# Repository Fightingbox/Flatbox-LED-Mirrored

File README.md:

# Flatbox-LED-Mirrored
Based on the [GP2040-CE](https://github.com/OpenStickCommunity/GP2040-CE) Flatbox Rev4

Add the colorful LEDs and the OLED display, perfect hardware change beased on the [Flatbox](https://github.com/jfedor2/flatbox) design by [jfedor2](https://github.com/jfedor2) powered by an RP2040 MCU.

## Upgrade the firmware:
- Unplug your device.
- Put your device into Bootsel/USB mode. A new removable drive named RPI-RP2 should appear in your file explorer.
- Drag and drop the GP2040-CE_XXX.uf2 firmware into the removable drive.
- Wait for the device to automatically disconnect.

### If you encounter problems updating firmware, please refer to the official firmware update [Tutorial](https://gp2040-ce.info/?spm=a2g0o.detail.1000023.2.163cu936u936KZ#/installation).

## GP2040-CE Links

[Downloads](https://gp2040-ce.info/#/download) | [Installation](https://gp2040-ce.info/#/installation) | [Wiring](https://gp2040-ce.info/#/wiring) | [Usage](https://gp2040-ce.info/#/usage) | [FAQ](https://gp2040-ce.info/#/faq) | [GitHub](https://github.com/OpenStickCommunity/GP2040-CE)

Full documentation can be found at <https://gp2040-ce.info>

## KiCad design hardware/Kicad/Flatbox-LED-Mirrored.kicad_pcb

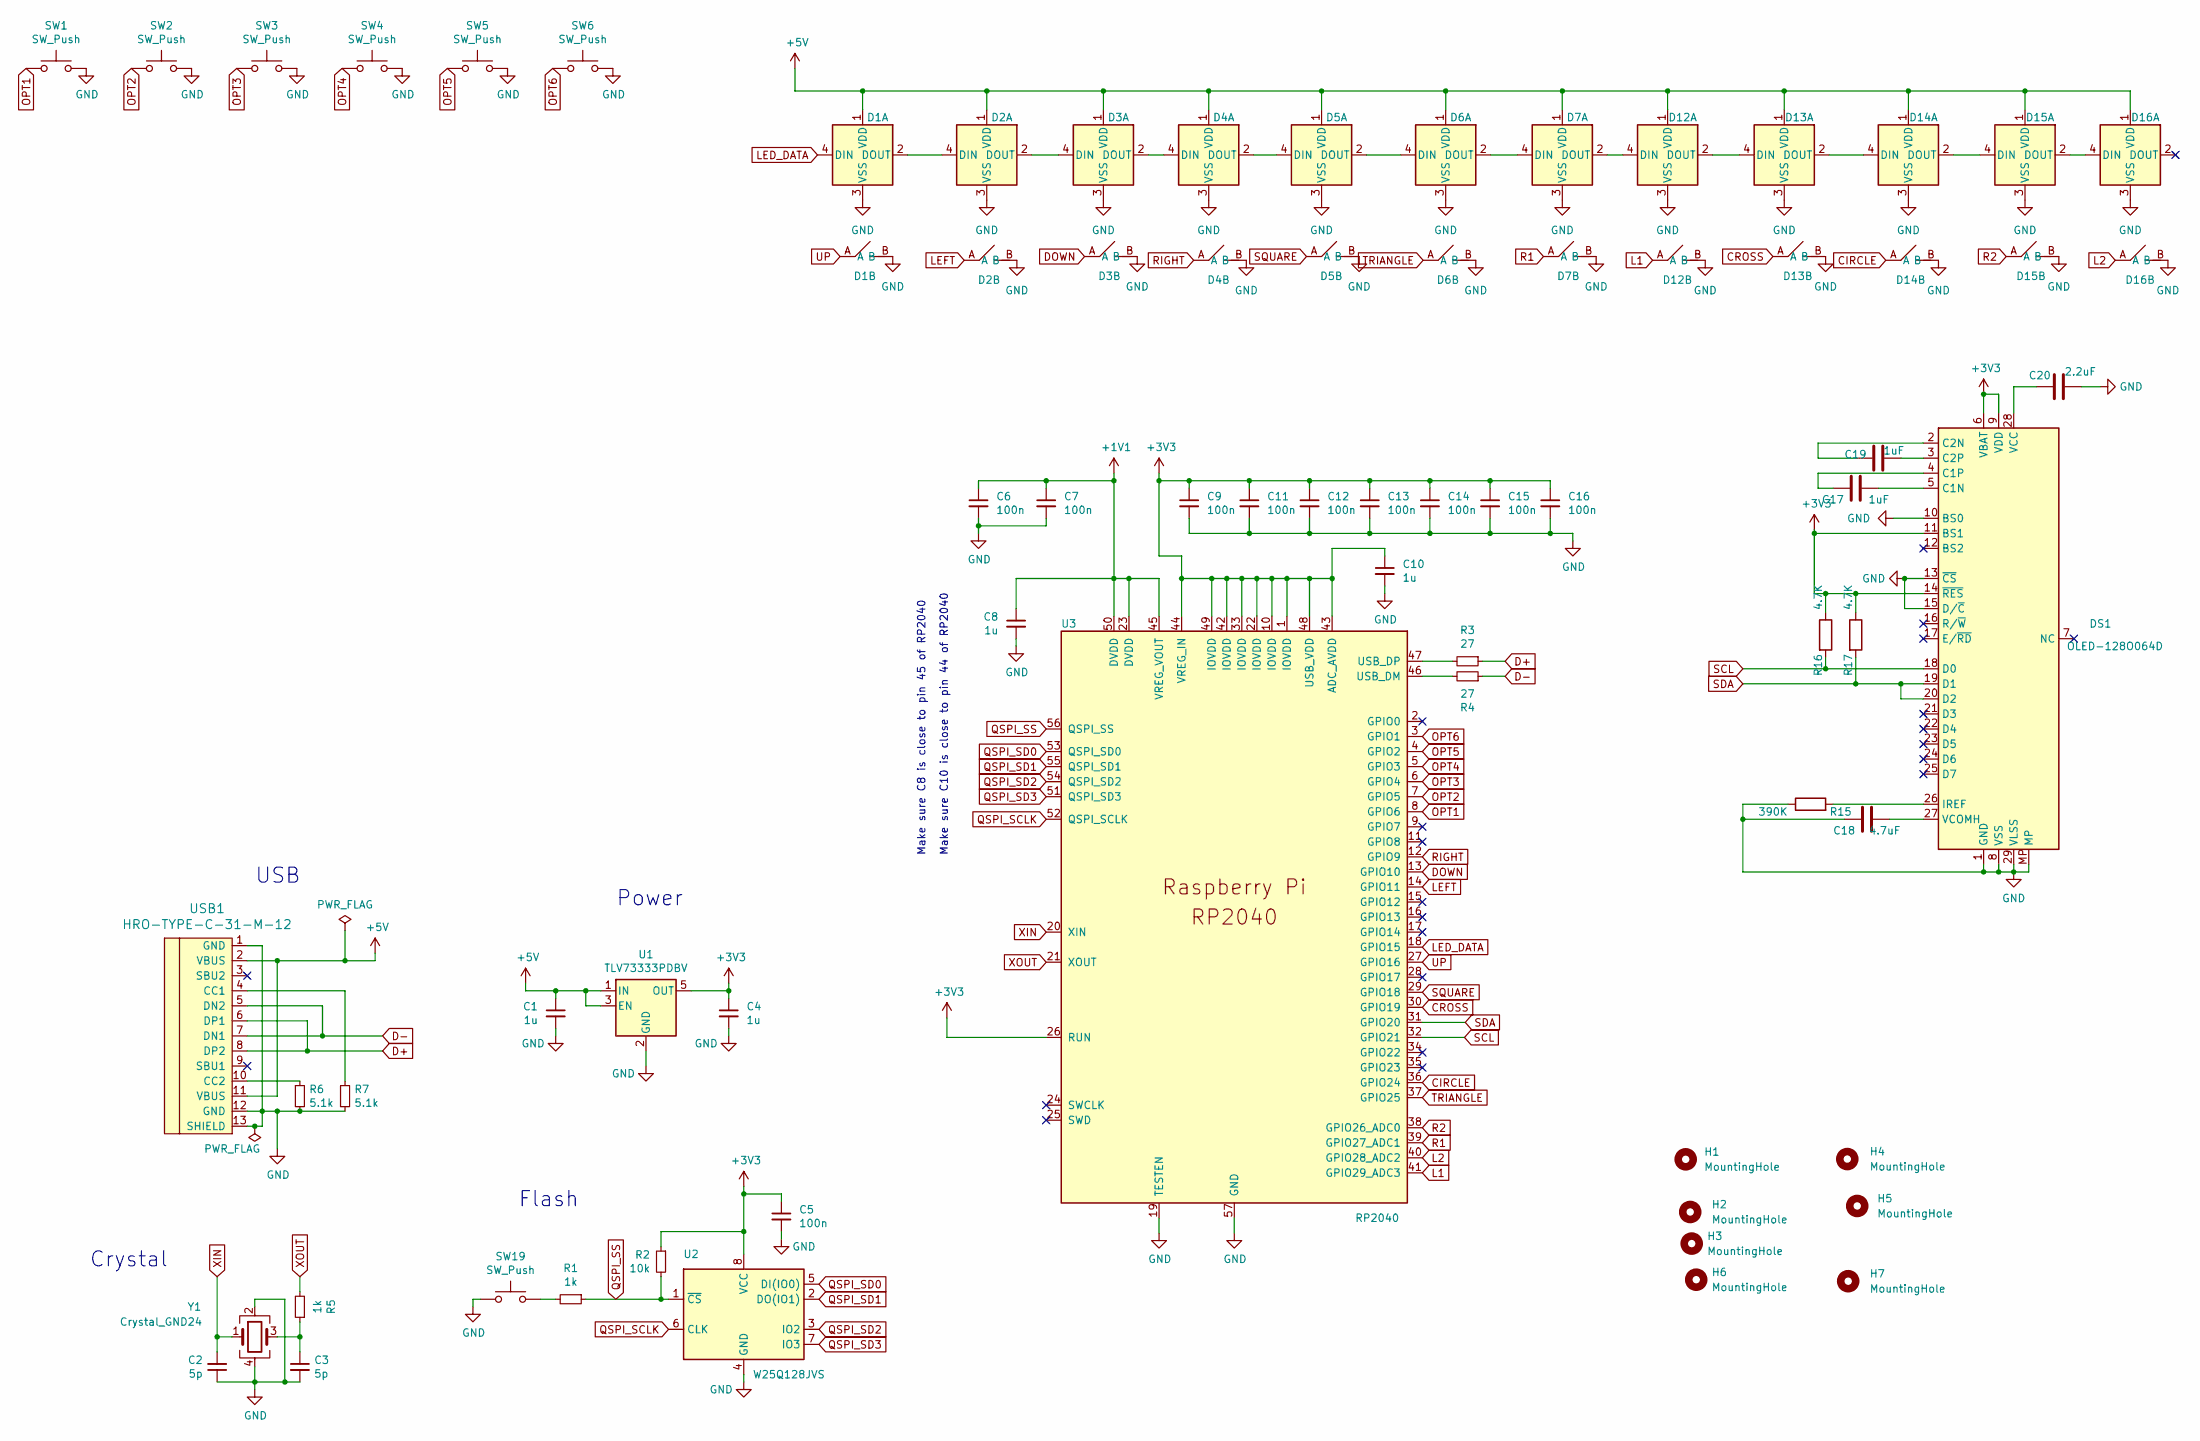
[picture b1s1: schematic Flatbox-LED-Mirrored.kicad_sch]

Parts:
C1, C4, C8, C10: 1u; C_0402_1005Metric; LCSC C52923
C2, C3: 5p; C_0402_1005Metric; LCSC C1570
C5, C6, C7, C9, C11, C12, C13, C14, C15, C16: 100n; C_0402_1005Metric; LCSC C1525
C17, C19: 1uF; C_0402_1005Metric
C18: 4.7uF; C_0603_1608Metric
C20: 2.2uF; C_0603_1608Metric
D1, D2, D3, D4, D5, D6, D7, D12, D13, D14, D15, D16: KB_HOTSWAP_WS2812B; Kailh_socket_PG1353_LED_1U
DS1: OLED-128O064D; TE_CON-0_1x30-1MP_P0.5mm_Horizontal-OLED-FPC
H1, H2, H3, H4, H5, H6, H7: MountingHole; MountingHole_6mm
R1, R5: 1k; R_0402_1005Metric; LCSC C11702
R2: 10k; R_0402_1005Metric; LCSC C25744
R3, R4: 27; R_0402_1005Metric; LCSC C138021
R6, R7: 5.1k; R_0402_1005Metric; LCSC C25905
R15: 390K; R_0402_1005Metric
R16, R17: 4.7K; R_0402_1005Metric
SW1, SW2, SW3, SW4, SW5, SW6: SW_Push; SW_Push_1P1T_NO_6x6mm_H5mm
SW19: SW_Push; SW-K2-1109SE; LCSC C271750
U1: TLV73333PDBV; SOT-23-5; LCSC C134139
U2: W25Q128JVS; SOIC-8_5.23x5.23mm_P1.27mm; LCSC C97521
U3: RP2040; RP2040-QFN-56; LCSC C2040
USB1: HRO-TYPE-C-31-M-12; HRO-TYPE-C-31-M-12-Assembly; LCSC C165948
Y1: Crystal_GND24; Crystal_SMD_3225-4Pin_3.2x2.5mm; LCSC C9002

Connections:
+1V1: C6.1, C7.1, C8.1, U3.23 (DVDD), U3.45 (VREG_VOUT), U3.50 (DVDD)
+3V3: C4.1, C5.1, C9.1, C10.1, C11.1, C12.1, C13.1, C14.1, C15.1, C16.1, DS1.6 (VBAT), DS1.9 (VDD), DS1.11 (BS1), DS1.14 (~RES), R2.1, R16.1, R17.1, U1.5 (OUT), U2.8 (VCC), U3.1 (IOVDD), U3.10 (IOVDD), U3.22 (IOVDD), U3.26 (RUN), U3.33 (IOVDD), U3.42 (IOVDD), U3.43 (ADC_AVDD), U3.44 (VREG_IN), U3.48 (USB_VDD), U3.49 (IOVDD)
+5V: C1.1, D1.1 (VDD), D2.1 (VDD), D3.1 (VDD), D4.1 (VDD), D5.1 (VDD), D6.1 (VDD), D7.1 (VDD), D12.1 (VDD), D13.1 (VDD), D14.1 (VDD), D15.1 (VDD), D16.1 (VDD), U1.1 (IN), U1.3 (EN), USB1.2 (VBUS), USB1.11 (VBUS)
CIRCLE: D14.A, U3.36 (GPIO24)
CROSS: D13.A, U3.30 (GPIO19)
D+: R3.1, USB1.6 (DP1), USB1.8 (DP2)
D-: R4.1, USB1.5 (DN2), USB1.7 (DN1)
DOWN: D3.A, U3.13 (GPIO10)
GND: C1.2, C2.1, C3.2, C4.2, C5.2, C6.2, C7.2, C8.2, C9.2, C10.2, C11.2, C12.2, C13.2, C14.2, C15.2, C16.2, C18.1, C20.2, D1.3 (VSS), D1.B, D2.3 (VSS), D2.B, D3.3 (VSS), D3.B, D4.3 (VSS), D4.B, D5.3 (VSS), D5.B, D6.3 (VSS), D6.B, D7.3 (VSS), D7.B, D12.3 (VSS), D12.B, D13.3 (VSS), D13.B, D14.3 (VSS), D14.B, D15.3 (VSS), D15.B, D16.3 (VSS), D16.B, DS1.1 (GND), DS1.8 (VSS), DS1.10 (BS0), DS1.13 (~CS), DS1.15 (D/~C), DS1.29 (VLSS), DS1.30 (GND), DS1.MP, R6.2, R7.2, R15.1, SW1.2, SW2.2, SW3.2, SW4.2, SW5.2, SW6.2, SW19.1, SW19.GND, U1.2 (GND), U2.4 (GND), U3.19 (TESTEN), U3.57 (GND), USB1.1 (GND), USB1.12 (GND), USB1.13 (SHIELD), Y1.2, Y1.4
L1: D12.A, U3.41 (GPIO29_ADC3)
L2: D16.A, U3.40 (GPIO28_ADC2)
LED_DATA: D1.4 (DIN), U3.18 (GPIO15)
unnamed: C3.1, R5.1, Y1.3
unnamed: D1.2 (DOUT), D2.4 (DIN)
unnamed: D2.2 (DOUT), D3.4 (DIN)
unnamed: D3.2 (DOUT), D4.4 (DIN)
unnamed: D4.2 (DOUT), D5.4 (DIN)
unnamed: D5.2 (DOUT), D6.4 (DIN)
unnamed: D6.2 (DOUT), D7.4 (DIN)
unnamed: D7.2 (DOUT), D12.4 (DIN)
unnamed: D12.2 (DOUT), D13.4 (DIN)
unnamed: D13.2 (DOUT), D14.4 (DIN)
unnamed: D14.2 (DOUT), D15.4 (DIN)
unnamed: D15.2 (DOUT), D16.4 (DIN)
unnamed: C17.2, DS1.5 (C1N)
unnamed: C17.1, DS1.4 (C1P)
unnamed: C19.1, DS1.2 (C2N)
unnamed: C19.2, DS1.3 (C2P)
unnamed: DS1.26 (IREF), R15.2
unnamed: C20.1, DS1.28 (VCC)
unnamed: C18.2, DS1.27 (VCOMH)
unnamed: R1.2, SW19.2
unnamed: R4.2, U3.46 (USB_DM)
unnamed: R3.2, U3.47 (USB_DP)
unnamed: R7.1, USB1.4 (CC1)
unnamed: R6.1, USB1.10 (CC2)
OPT1: SW1.1, U3.8 (GPIO6)
OPT2: SW2.1, U3.7 (GPIO5)
OPT3: SW3.1, U3.6 (GPIO4)
OPT4: SW4.1, U3.5 (GPIO3)
OPT5: SW5.1, U3.4 (GPIO2)
OPT6: SW6.1, U3.3 (GPIO1)
QSPI_SCLK: U2.6 (CLK), U3.52 (QSPI_SCLK)
QSPI_SD0: U2.5 (DI(IO0)), U3.53 (QSPI_SD0)
QSPI_SD1: U2.2 (DO(IO1)), U3.55 (QSPI_SD1)
QSPI_SD2: U2.3 (IO2), U3.54 (QSPI_SD2)
QSPI_SD3: U2.7 (IO3), U3.51 (QSPI_SD3)
QSPI_SS: R1.1, R2.2, U2.1 (~CS), U3.56 (QSPI_SS)
R1: D7.A, U3.39 (GPIO27_ADC1)
R2: D15.A, U3.38 (GPIO26_ADC0)
SCL: DS1.18 (D0), R16.2, U3.32 (GPIO21)
SDA: DS1.19 (D1), DS1.20 (D2), R17.2, U3.31 (GPIO20)
SQUARE: D5.A, U3.29 (GPIO18)
TRIANGLE: D6.A, U3.37 (GPIO25)
UP: D1.A, U3.27 (GPIO16)
XIN: C2.2, U3.20 (XIN), Y1.1
XOUT: R5.2, U3.21 (XOUT)

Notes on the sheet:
Make sure C10 is close to pin 44 of RP2040
Crystal
Flash
Make sure C8 is close to pin 45 of RP2040
USB
Power

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
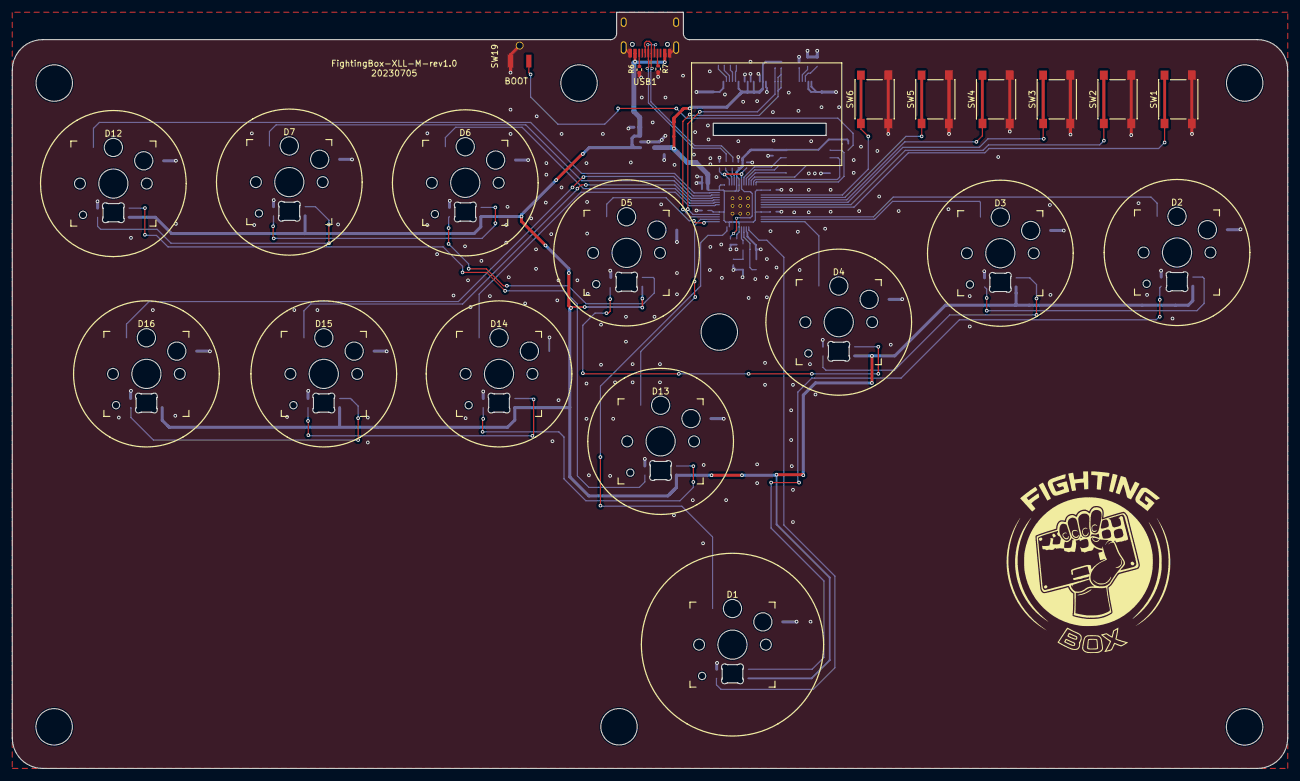
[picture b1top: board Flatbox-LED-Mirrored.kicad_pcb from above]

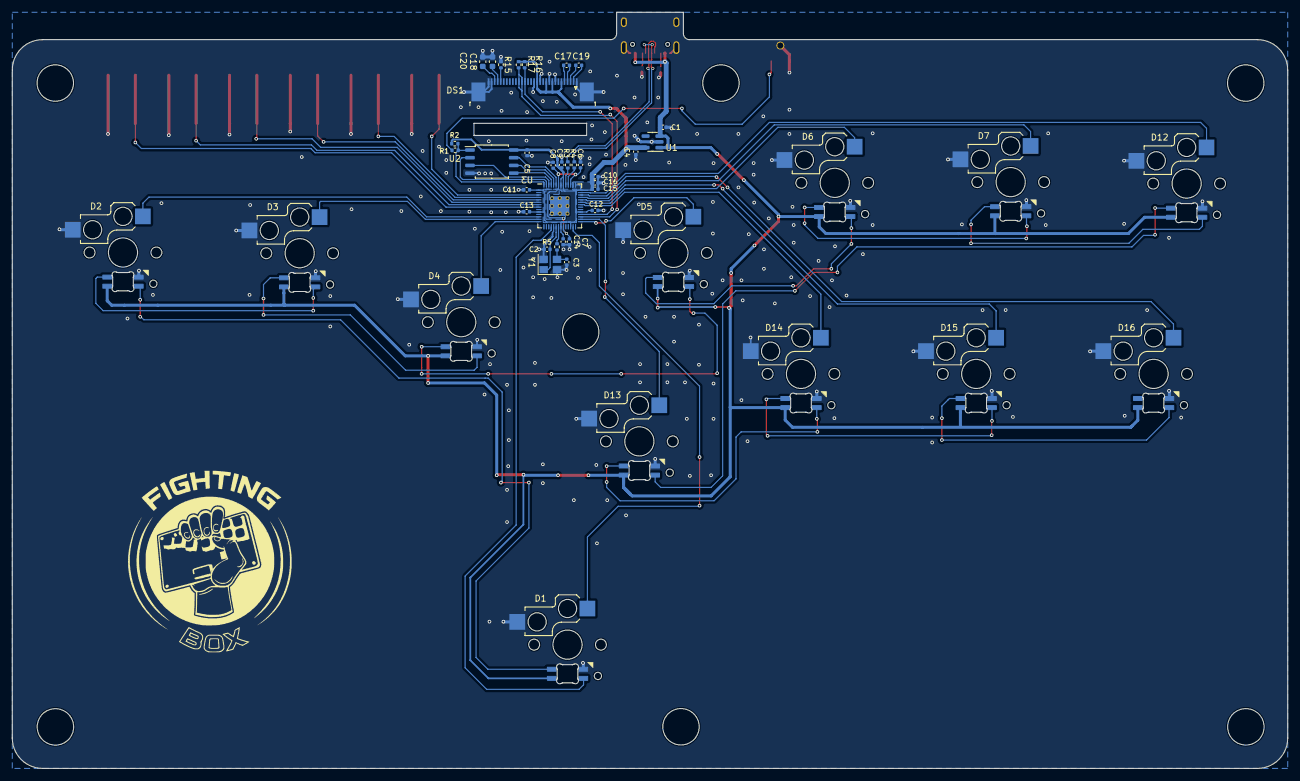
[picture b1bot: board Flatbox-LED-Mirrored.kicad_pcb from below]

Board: 2 copper layers, 209.9 x 124.4 mm, 62 parts (40 on the bottom side), 59 nets.

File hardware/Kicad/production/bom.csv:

Designator,Footprint,Quantity,Value,LCSC Part #
"C1, C10, C4, C8",0402,4,1u,C52923
"C11, C12, C13, C14, C15, C16, C5, C6, C7, C9",0402,10,100n,C1525
"C17, C19",0402,2,1uF, 
C18,0603,1,4.7uF, 
"C2, C3",0402,2,5p,C1570
C20,0603,1,2.2uF, 
"D1, D12, D13, D14, D15, D16, D2, D3, D4, D5, D6, D7",Kailh_socket_PG1353_LED_1U-4.8MM,12,KB_HOTSWAP_WS2812B,
DS1,TE_CON-0_1x30-1MP_P0.5mm_Horizontal-OLED-FPC,1,OLED-128O064D,
"H1, H2, H3, H4, H5, H6, H7",MountingHole_6mm,7,MountingHole,
"R1, R5",0402,2,1k,C11702
R15,0402,1,390K, 
"R16, R17",0402,2,4.7K, 
R2,0402,1,10k,C25744
"R3, R4",0402,2,27,C138021
"R6, R7",0402,2,5.1k,C25905
"SW1, SW2, SW3, SW4, SW5, SW6",SW_Push_1P1T_NO_6x6mm_H5mm,6,SW_Push,
SW19,SW-K2-1109SE,1,SW_Push,C271750
U1,SOT-23-5,1,TLV73333PDBV,C134139
U2,SOIC-8_5.23x5.23mm_P1.27mm,1,W25Q128JVS,C97521
U3,RP2040-QFN-56,1,RP2040,C2040
USB1,HRO-TYPE-C-31-M-12-Assembly,1,HRO-TYPE-C-31-M-12,C165948
Y1,Crystal_SMD_3225-4Pin_3.2x2.5mm,1,Crystal_GND24,C9002

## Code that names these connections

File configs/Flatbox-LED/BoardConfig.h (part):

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#define GPIO_PIN_10 GpioAction::BUTTON_PRESS_DOWN   // DOWN   | DOWN   | DOWN    | DOWN     | DOWN   | DOWN   |
#define GPIO_PIN_11 GpioAction::BUTTON_PRESS_RIGHT  // RIGHT  | RIGHT  | RIGHT   | RIGHT    | RIGHT  | RIGHT  |
#define GPIO_PIN_09 GpioAction::BUTTON_PRESS_LEFT   // LEFT   | LEFT   | LEFT    | LEFT     | LEFT   | LEFT   |
#define GPIO_PIN_19 GpioAction::BUTTON_PRESS_B1     // B1     | A      | B       | Cross    | 2      | K1     |
#define GPIO_PIN_24 GpioAction::BUTTON_PRESS_B2     // B2     | B      | A       | Circle   | 3      | K2     |
#define GPIO_PIN_26 GpioAction::BUTTON_PRESS_R2     // R2     | RT     | ZR      | R2       | 8      | K3     |
#define GPIO_PIN_28 GpioAction::BUTTON_PRESS_L2     // L2     | LT     | ZL      | L2       | 7      | K4     |
#define GPIO_PIN_18 GpioAction::BUTTON_PRESS_B3     // B3     | X      | Y       | Square   | 1      | P1     |
#define GPIO_PIN_25 GpioAction::BUTTON_PRESS_B4     // B4     | Y      | X       | Triangle | 4      | P2     |
#define GPIO_PIN_27 GpioAction::BUTTON_PRESS_R1     // R1     | RB     | R       | R1       | 6      | P3     |
#define GPIO_PIN_29 GpioAction::BUTTON_PRESS_L1     // L1     | LB     | L       | L1       | 5      | P4     |
#define GPIO_PIN_05 GpioAction::BUTTON_PRESS_S1     // S1     | Back   | Minus   | Select   | 9      | Coin   |
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#define KEY_DPAD_DOWN   HID_KEY_ARROW_DOWN    // DOWN   | DOWN   | DOWN    | DOWN     | DOWN   | DOWN   |
#define KEY_DPAD_RIGHT  HID_KEY_ARROW_RIGHT   // RIGHT  | RIGHT  | RIGHT   | RIGHT    | RIGHT  | RIGHT  |
#define KEY_DPAD_LEFT   HID_KEY_ARROW_LEFT    // LEFT   | LEFT   | LEFT    | LEFT     | LEFT   | LEFT   |
#define KEY_BUTTON_B1   HID_KEY_SHIFT_LEFT    // B1     | A      | B       | Cross    | 2      | K1     |
#define KEY_BUTTON_B2   HID_KEY_Z             // B2     | B      | A       | Circle   | 3      | K2     |
#define KEY_BUTTON_R2   HID_KEY_X             // R2     | RT     | ZR      | R2       | 8      | K3     |
#define KEY_BUTTON_L2   HID_KEY_V             // L2     | LT     | ZL      | L2       | 7      | K4     |
#define KEY_BUTTON_B3   HID_KEY_CONTROL_LEFT  // B3     | X      | Y       | Square   | 1      | P1     |
#define KEY_BUTTON_B4   HID_KEY_ALT_LEFT      // B4     | Y      | X       | Triangle | 4      | P2     |
#define KEY_BUTTON_R1   HID_KEY_SPACE         // R1     | RB     | R       | R1       | 6      | P3     |
#define KEY_BUTTON_L1   HID_KEY_C             // L1     | LB     | L       | L1       | 5      | P4     |
#define KEY_BUTTON_S1   HID_KEY_5             // S1     | Back   | Minus   | Select   | 9      | Coin   |
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
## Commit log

2023-10-27 update pictures
2023-10-27 udpate readme
2024-01-19 flatbox led update to v0.7.7
2024-01-22 add the oled splash for Flatbox-LED
2024-03-26 fix the Dpad left right keys
2024-03-26 open source the PCB and the 3D print Case

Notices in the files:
configs/Flatbox-LED/BoardConfig.h:
SPDX-License-Identifier: MIT
SPDX-FileCopyrightText: Copyright (c) 2024 OpenStickCommunity (gp2040-ce.info)
